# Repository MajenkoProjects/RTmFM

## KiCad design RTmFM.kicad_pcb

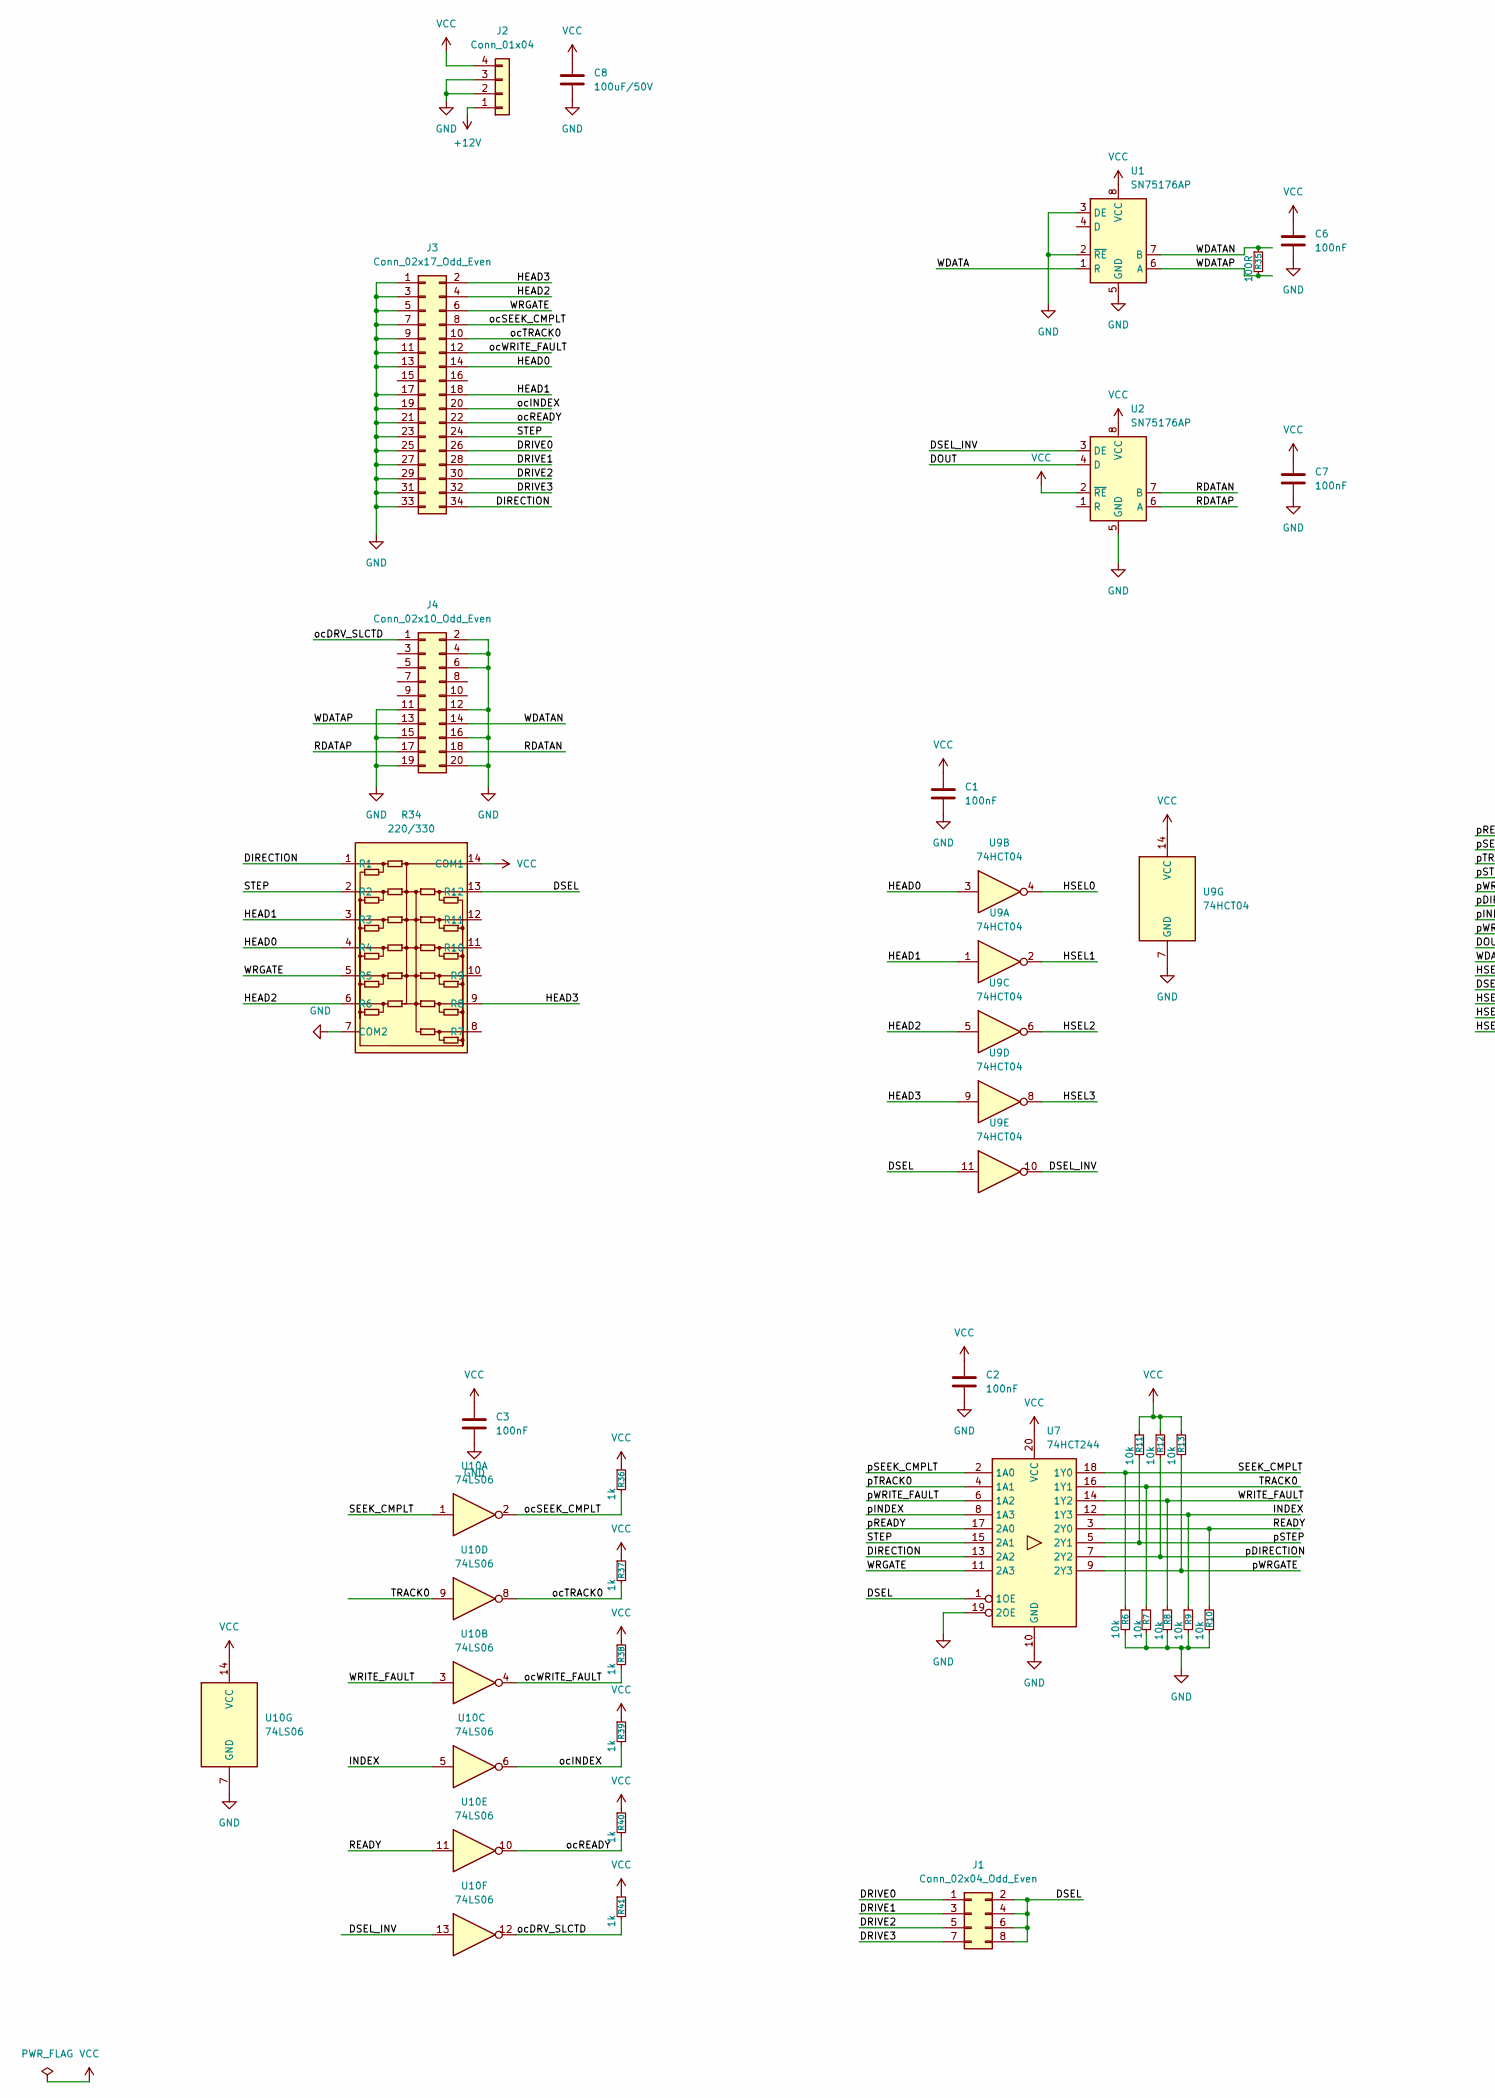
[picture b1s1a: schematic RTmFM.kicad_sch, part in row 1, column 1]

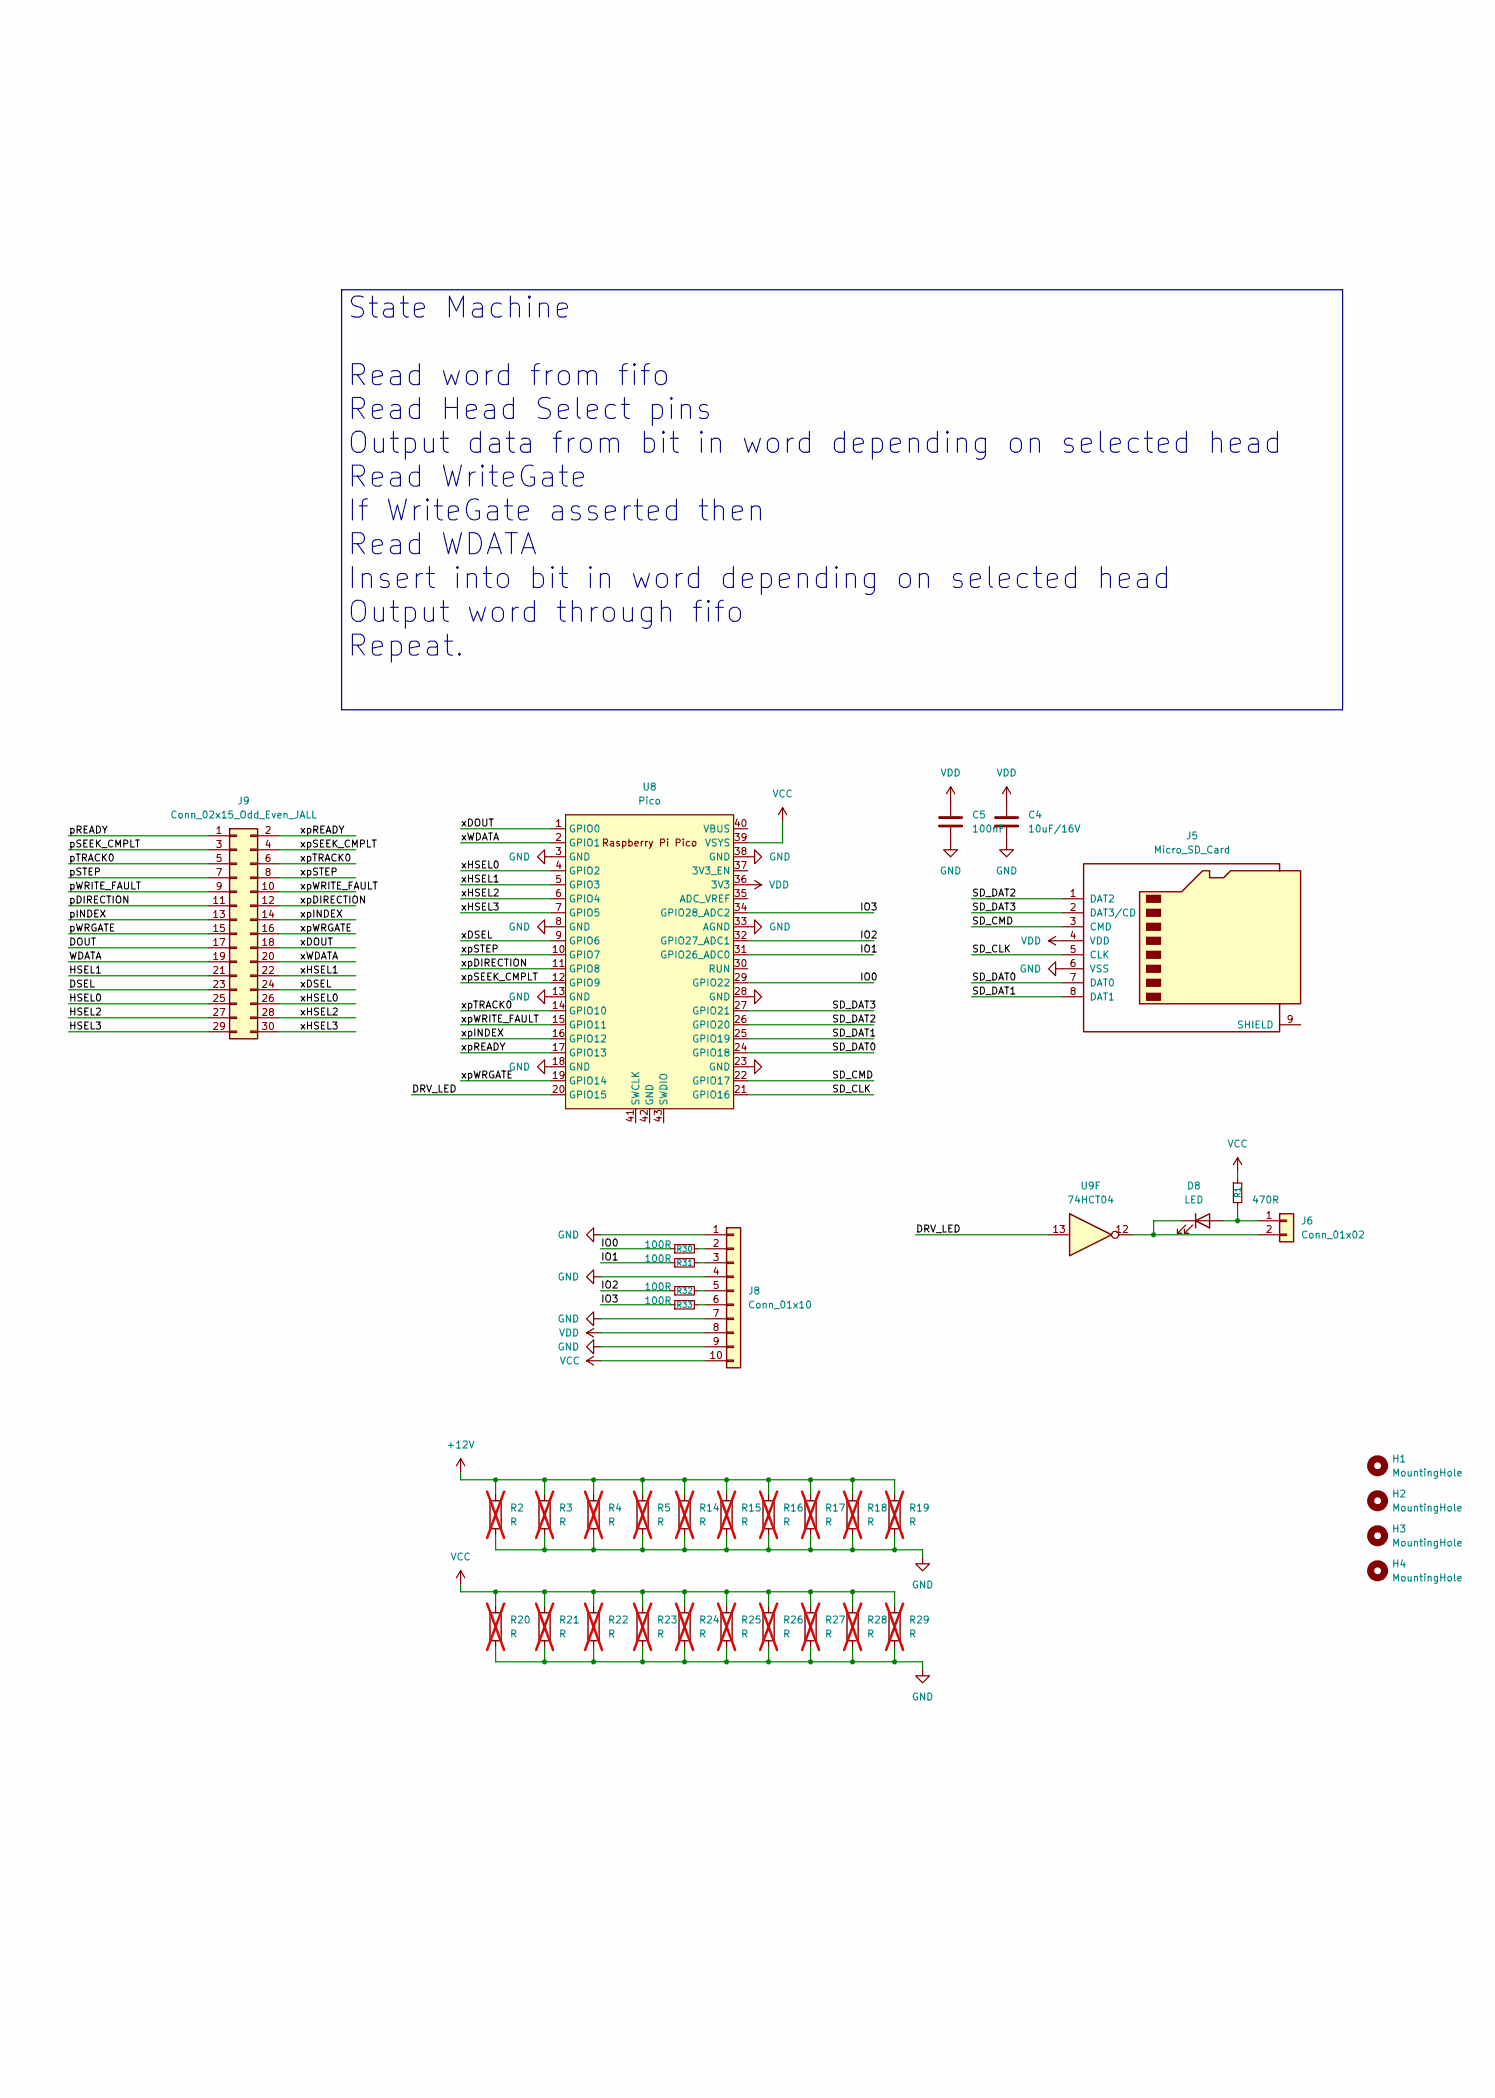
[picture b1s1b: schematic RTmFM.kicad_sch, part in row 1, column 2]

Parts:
C1, C2, C3, C5, C6, C7: 100nF; C_Disc_D7.5mm_W2.5mm_P5.00mm
C4: 10uF/16V; CP_Radial_D5.0mm_P2.50mm
C8: 100uF/50V; CP_Radial_D8.0mm_P3.50mm
D8: LED; LED_Rectangular_W5.0mm_H2.0mm_Horizontal_O3.81mm_Z3.0mm
H1, H2, H3, H4: MountingHole; MountingHole_3.2mm_M3_DIN965_Pad_TopBottom
J1: Conn_02x04_Odd_Even; PinHeader_2x04_P2.54mm_Vertical
J2: Conn_01x04; TE_MATE-N-LOK_350211-1_1x04_P5.08mm_Vertical
J3: Conn_02x17_Odd_Even; PCB Edge 2.54 pitch 34 pin
J4: Conn_02x10_Odd_Even; PCB Edge 2.54 pitch 20 pin
J5: Micro_SD_Card; 503182-1852_MOL
J6: Conn_01x02; PinHeader_1x02_P2.54mm_Vertical
J8: Conn_01x10; PinHeader_1x10_P2.54mm_Vertical
J9: Conn_02x15_Odd_Even_JALL; PinHeader_2x15_P2.54mm_Vertical
R1: 470R; R_Axial_DIN0204_L3.6mm_D1.6mm_P7.62mm_Horizontal
R2, R3, R4, R5, R14, R15, R16, R17, R18, R19, R20, R21, R22, R23, R24, R25, R26, R27, R28, R29: R; R_Axial_Power_L20.0mm_W6.4mm_P25.40mm; not fitted
R6, R7, R8, R9, R10, R11, R12, R13: 10k; R_Axial_DIN0204_L3.6mm_D1.6mm_P7.62mm_Horizontal
R30, R31, R32, R33, R35: 100R; R_Axial_DIN0204_L3.6mm_D1.6mm_P7.62mm_Horizontal
R34: 220/330; DIP-14_W7.62mm_Socket
R36, R37, R38, R39, R40, R41: 1k; R_Axial_DIN0204_L3.6mm_D1.6mm_P7.62mm_Horizontal
U1, U2: SN75176AP; DIP-8_W7.62mm
U7: 74HCT244; DIP-20_W7.62mm
U8: Pico; RaspberryPi_Pico_Common_THT
U9: 74HCT04; DIP-14_W7.62mm
U10: 74LS06; DIP-14_W7.62mm

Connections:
+12V: J2.1, R2.1, R3.1, R4.1, R5.1, R14.1, R15.1, R16.1, R17.1, R18.1, R19.1
/DIRECTION: J3.34, R34.1 (R1), U7.13 (2A2)
/DOUT: J9.17, U2.4 (D)
/DRIVE0: J1.1, J3.26
/DRIVE1: J1.3, J3.28
/DRIVE2: J1.5, J3.30
/DRIVE3: J1.7, J3.32
/DRV_LED: U8.20 (GPIO15), U9.13
/DSEL: J1.2, J1.4, J1.6, J1.8, J9.23, R34.13 (R12), U7.1 (1OE), U9.11
/DSEL_INV: U2.3 (DE), U9.10, U10.13
/HEAD0: J3.14, R34.4 (R4), U9.3
/HEAD1: J3.18, R34.3 (R3), U9.1
/HEAD2: J3.4, R34.6 (R6), U9.5
/HEAD3: J3.2, R34.9 (R8), U9.9
/HSEL0: J9.25, U9.4
/HSEL1: J9.21, U9.2
/HSEL2: J9.27, U9.6
/HSEL3: J9.29, U9.8
/INDEX: R9.1, U7.12 (1Y3), U10.5
/IO0: R30.1, U8.29 (GPIO22)
/IO1: R31.1, U8.31 (GPIO26_ADC0)
/IO2: R32.1, U8.32 (GPIO27_ADC1)
/IO3: R33.1, U8.34 (GPIO28_ADC2)
/RDATAN: J4.18, U2.7 (B)
/RDATAP: J4.17, U2.6 (A)
/READY: R10.1, U7.3 (2Y0), U10.11
/SD_CLK: J5.5 (CLK), U8.21 (GPIO16)
/SD_CMD: J5.3 (CMD), U8.22 (GPIO17)
/SD_DAT0: J5.7 (DAT0), U8.24 (GPIO18)
/SD_DAT1: J5.8 (DAT1), U8.25 (GPIO19)
/SD_DAT2: J5.1 (DAT2), U8.26 (GPIO20)
/SD_DAT3: J5.2 (DAT3/CD), U8.27 (GPIO21)
/SEEK_CMPLT: R6.1, U7.18 (1Y0), U10.1
/STEP: J3.24, R34.2 (R2), U7.15 (2A1)
/TRACK0: R7.1, U7.16 (1Y1), U10.9
/WDATA: J9.19, U1.1 (R)
/WDATAN: J4.14, R35.1, U1.7 (B)
/WDATAP: J4.13, R35.2, U1.6 (A)
/WRGATE: J3.6, R34.5 (R5), U7.11 (2A3)
/WRITE_FAULT: R8.1, U7.14 (1Y2), U10.3
/ocDRV_SLCTD: J4.1, R41.2, U10.12
/ocINDEX: J3.20, R39.2, U10.6
/ocREADY: J3.22, R40.2, U10.10
/ocSEEK_CMPLT: J3.8, R36.2, U10.2
/ocTRACK0: J3.10, R37.2, U10.8
/ocWRITE_FAULT: J3.12, R38.2, U10.4
/pDIRECTION: J9.11, R12.2, U7.7 (2Y2)
/pINDEX: J9.13, U7.8 (1A3)
/pREADY: J9.1, U7.17 (2A0)
/pSEEK_CMPLT: J9.3, U7.2 (1A0)
/pSTEP: J9.7, R11.2, U7.5 (2Y1)
/pTRACK0: J9.5, U7.4 (1A1)
/pWRGATE: J9.15, R13.2, U7.9 (2Y3)
/pWRITE_FAULT: J9.9, U7.6 (1A2)
/xDOUT: J9.18, U8.1 (GPIO0)
/xDSEL: J9.24, U8.9 (GPIO6)
/xHSEL0: J9.26, U8.4 (GPIO2)
/xHSEL1: J9.22, U8.5 (GPIO3)
/xHSEL2: J9.28, U8.6 (GPIO4)
/xHSEL3: J9.30, U8.7 (GPIO5)
/xWDATA: J9.20, U8.2 (GPIO1)
/xpDIRECTION: J9.12, U8.11 (GPIO8)
/xpINDEX: J9.14, U8.16 (GPIO12)
/xpREADY: J9.2, U8.17 (GPIO13)
/xpSEEK_CMPLT: J9.4, U8.12 (GPIO9)
/xpSTEP: J9.8, U8.10 (GPIO7)
/xpTRACK0: J9.6, U8.14 (GPIO10)
/xpWRGATE: J9.16, U8.19 (GPIO14)
/xpWRITE_FAULT: J9.10, U8.15 (GPIO11)
GND: C1.2, C2.2, C3.2, C4.2, C5.2, C6.2, C7.2, C8.2, J2.2, J2.3, J3.1, J3.3, J3.5, J3.7, J3.9, J3.11, J3.13, J3.17, J3.19, J3.21, J3.23, J3.25, J3.27, J3.29, J3.31, J3.33, J4.2, J4.4, J4.6, J4.11, J4.12, J4.15, J4.16, J4.19, J4.20, J5.6 (VSS), J8.1, J8.4, J8.7, J8.9, R2.2, R3.2, R4.2, R5.2, R6.2, R7.2, R8.2, R9.2, R10.2, R14.2, R15.2, R16.2, R17.2, R18.2, R19.2, R20.2, R21.2, R22.2, R23.2, R24.2, R25.2, R26.2, R27.2, R28.2, R29.2, R34.7 (COM2), U1.2 (~RE), U1.3 (DE), U1.5 (GND), U2.5 (GND), U7.10 (GND), U7.19 (2OE), U8.3 (GND), U8.8 (GND), U8.13 (GND), U8.18 (GND), U8.23 (GND), U8.28 (GND), U8.33 (AGND), U8.38 (GND), U9.7 (GND), U10.7 (GND)
unnamed: D8.2 (A), J6.1, R1.2
unnamed: D8.1 (K), J6.2, U9.12
unnamed: J8.2, R30.2
unnamed: J8.3, R31.2
unnamed: J8.5, R32.2
unnamed: J8.6, R33.2
VCC: C1.1, C2.1, C3.1, C6.1, C7.1, C8.1, J2.4, J8.10, R1.1, R11.1, R12.1, R13.1, R20.1, R21.1, R22.1, R23.1, R24.1, R25.1, R26.1, R27.1, R28.1, R29.1, R34.14 (COM1), R36.1, R37.1, R38.1, R39.1, R40.1, R41.1, U1.8 (VCC), U2.2 (~RE), U2.8 (VCC), U7.20 (VCC), U8.39 (VSYS), U9.14 (VCC), U10.14 (VCC)
VDD: C4.1, C5.1, J5.4 (VDD), J8.8, U8.36 (3V3)

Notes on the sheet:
State Machine Read word from fifo Read Head Select pins Output data from bit in word depending on selected head Read WriteGate If WriteGate asserted then Read WDATA Insert into bit in word depending on selected head Output word through fifo Repeat.

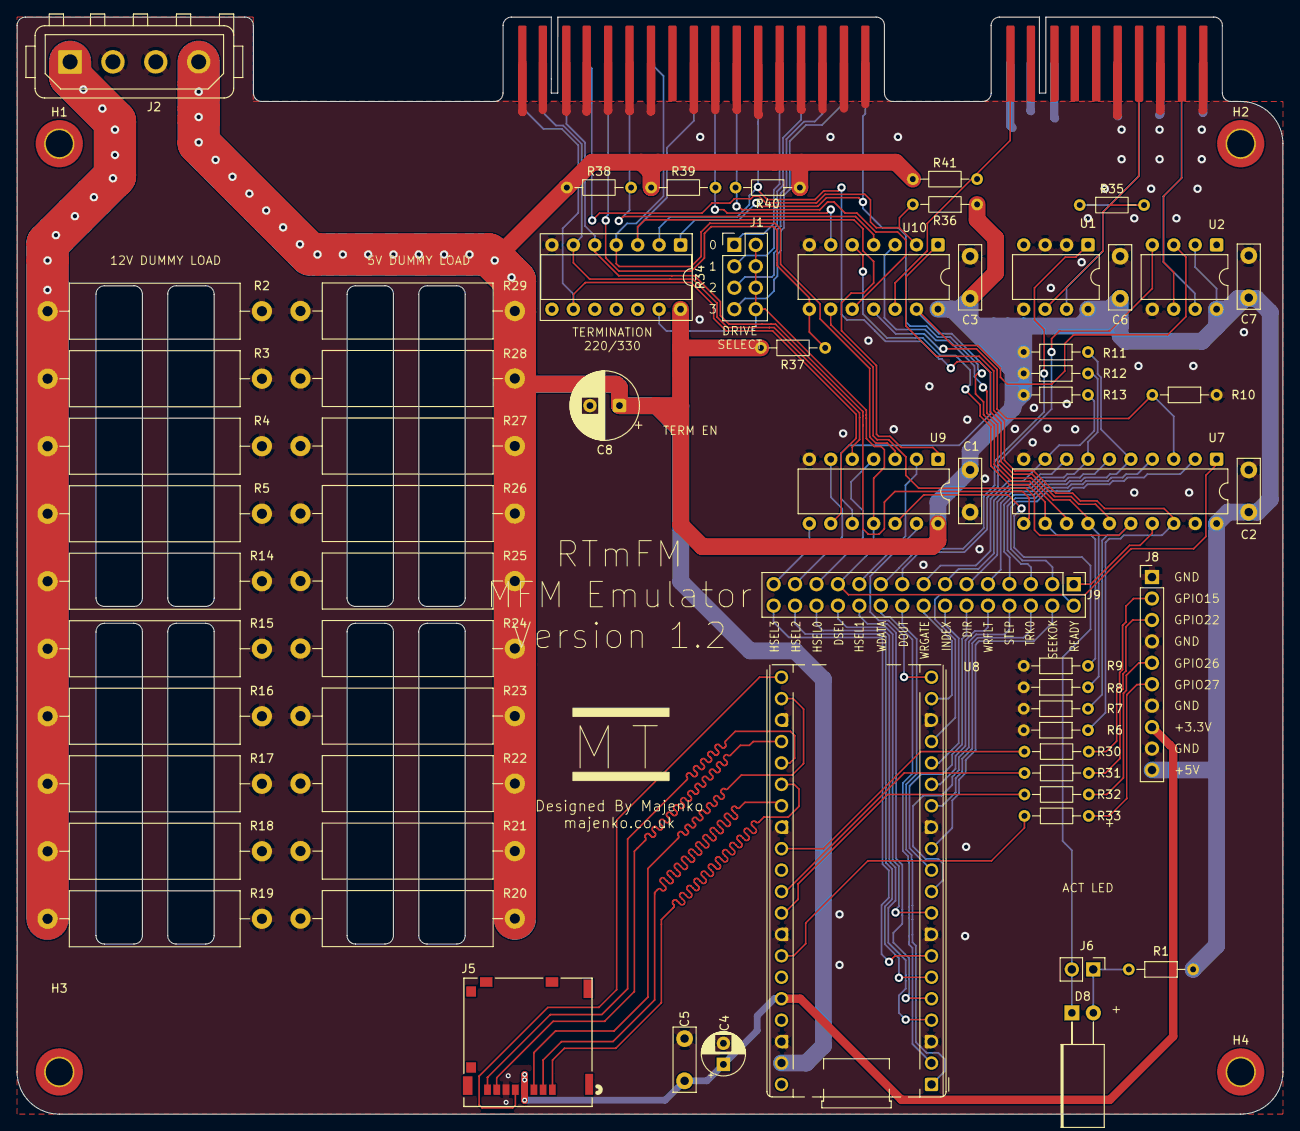
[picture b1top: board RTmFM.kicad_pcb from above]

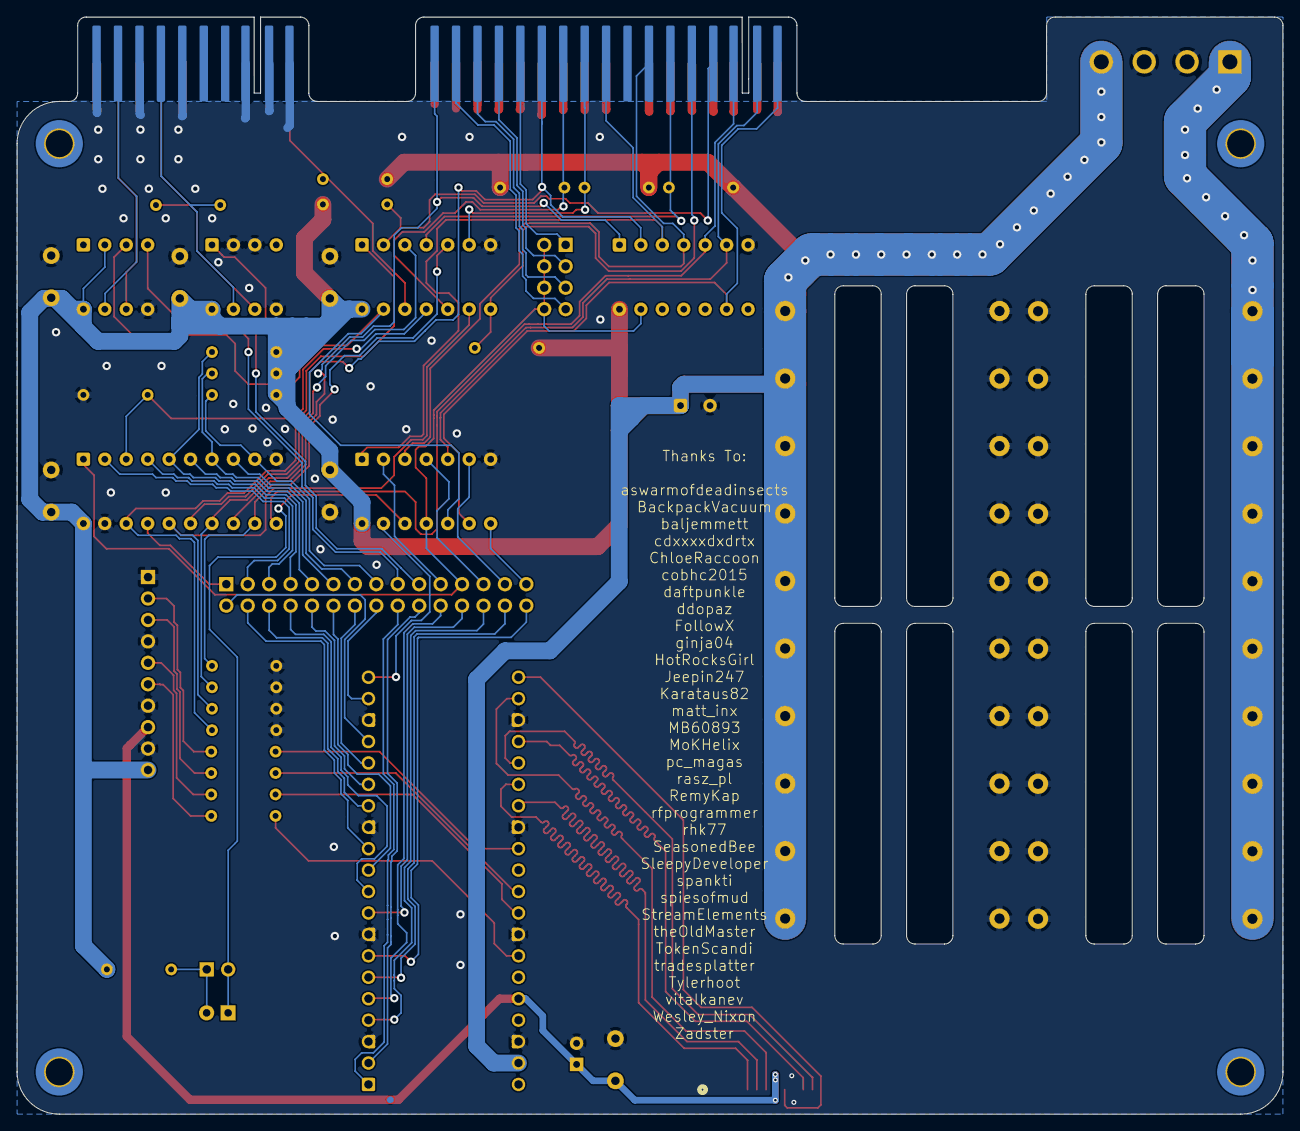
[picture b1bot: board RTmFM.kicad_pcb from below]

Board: 2 copper layers, 150.0 x 130.0 mm, 68 parts (2 on the bottom side), 78 nets.

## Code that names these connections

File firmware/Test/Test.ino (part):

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#define SECTOR_1024 3


#define INDEX			12
#define DOUT			0

#define STEP			7
#define DIR				8
#define SEEK_DONE		9
#define TRACK0			10

#define HSEL0			2
#define HSEL1			3
#define HSEL2			4
#define HSEL3			5

static PIOProgram datastreamPgm(&datastream_program);

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	struct encoded_sector *send = &sectorB;
	struct encoded_sector *swap;

	pinMode(HSEL0, INPUT);
	pinMode(HSEL1, INPUT);
	pinMode(HSEL2, INPUT);
	pinMode(HSEL3, INPUT);

	uint32_t cs = current_cyl;

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
	pio->txf[sm] = mfm_encode(0x00);

	pinMode(INDEX, OUTPUT);
	digitalWrite(INDEX, HIGH);
	Serial.begin(115200);

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	pinMode(DIR, INPUT);
	pinMode(SEEK_DONE, OUTPUT);
	digitalWrite(SEEK_DONE, HIGH);
	pinMode(TRACK0, OUTPUT);
	digitalWrite(TRACK0, current_cyl == 0);

	attachInterrupt(STEP, do_step, FALLING);
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
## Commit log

2025-05-01 Initial import
2025-05-02 Bus interface
2025-05-08 Fixed footprints and started layout
2025-05-15 Almost finished HW design
2025-05-19 End of version 1 design
2025-06-15 Exported
2025-09-03 Ability to transmit an MFM header block achieved
2025-09-03 Reversed bit ordering to make more sense
2025-09-04 Full track streaming and CLI interface
2025-09-04 Added ability to set CRC parameters
2025-09-05 Rework SD interface and add head 4
2025-09-05 Made loading concurrent
2025-09-06 Optimized data loading
2025-09-08 Version 1.1 rework
2025-10-23 Revision 1.1 and working data out
2026-02-12 Table based CRC and a few race protections
2026-02-12 Trying to fathom SM lockup on seek
2026-02-12 Found the seek bug at last (thanks ben)
2026-02-22 Added UIT and slice-4 CRC code
2026-05-27 Fixed bus interfacing
